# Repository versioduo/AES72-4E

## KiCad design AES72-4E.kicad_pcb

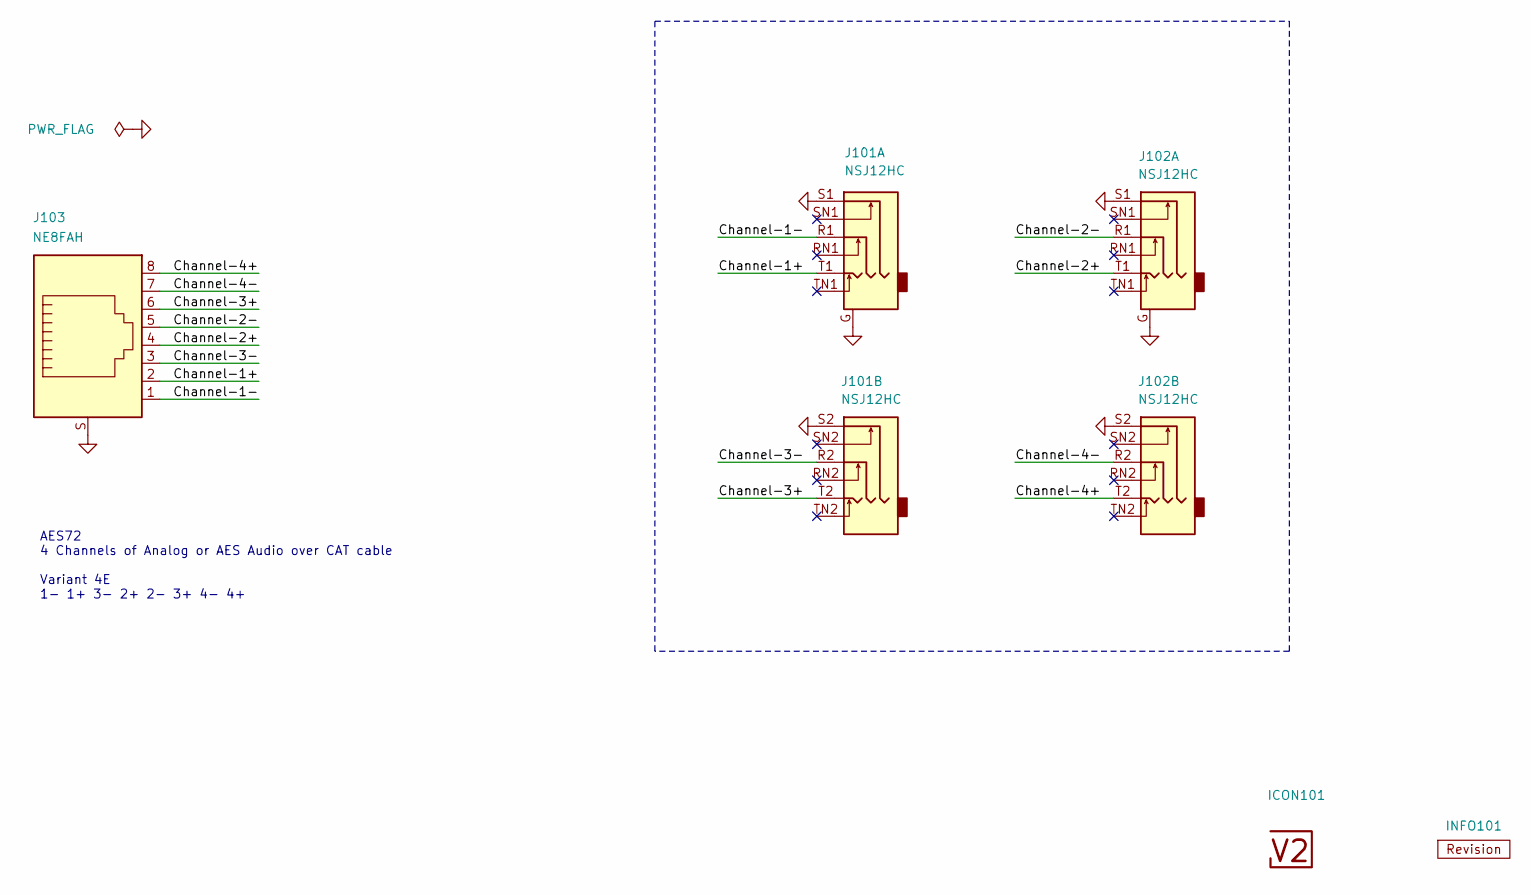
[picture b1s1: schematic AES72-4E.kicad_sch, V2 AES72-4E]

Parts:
ICON101: V2-logo; Logo_Small
INFO101: Revision
J101, J102: NSJ12HC; Jack_6.35mm_Neutrik_NSJ12HC_Horizontal; Rating 6.35mm; Mouser 568-NSJ12HC
J103: NE8FAH; Rating CAT5e; Mouser 568-NE8FAH

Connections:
/Channel-1+: J101.T1, J103.2
/Channel-1-: J101.R1, J103.1
/Channel-2+: J102.T1, J103.4
/Channel-2-: J102.R1, J103.5
/Channel-3+: J101.T2, J103.6
/Channel-3-: J101.R2, J103.3
/Channel-4+: J102.T2, J103.8
/Channel-4-: J102.R2, J103.7
GND: J101.G, J101.S1, J101.S2, J102.G, J102.S1, J102.S2, J103.S

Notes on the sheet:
AES72 4 Channels of Analog or AES Audio over CAT cable Variant 4E 1- 1+ 3- 2+ 2- 3+ 4- 4+

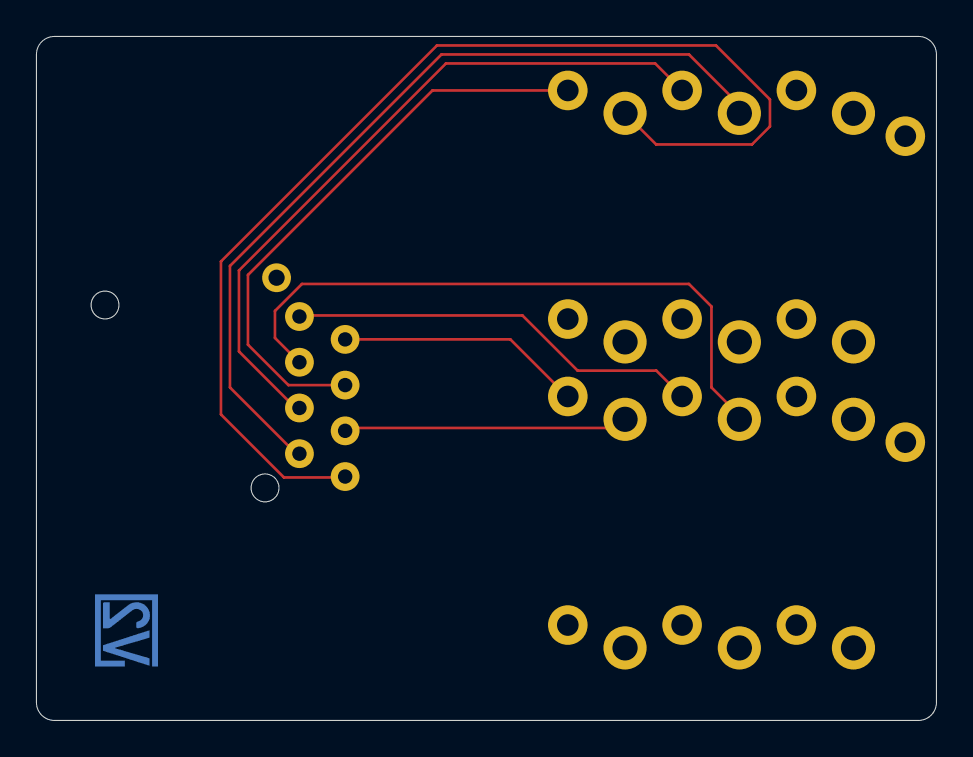
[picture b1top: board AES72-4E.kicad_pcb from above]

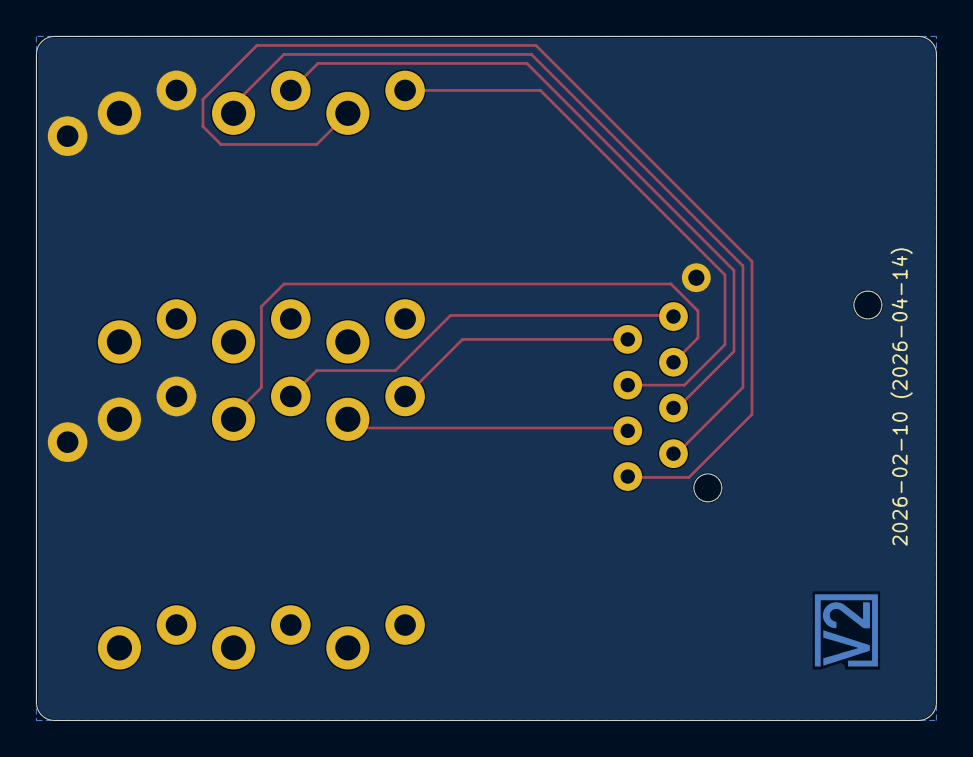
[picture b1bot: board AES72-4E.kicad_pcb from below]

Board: 2 copper layers, 50.0 x 38.0 mm, 5 parts (2 on the bottom side), 9 nets.

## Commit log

2026-02-13 Replace Order_Number
2026-02-15 Update Library
